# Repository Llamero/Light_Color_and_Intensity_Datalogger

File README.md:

# Data Logger: Temperature, Pressure, Humidity, Light Intensity and Color

## Summary:

This is an open-source data logger that can record air temperature, air pressure, relative humidity, visible light instensity, near-infrared light intensity, and visible light color (RGB).  This data logger can record at up to 1 Hz onto a FAT32 formatted SD card.  At 1Hz and with a full battery pack (6 AAs) the data logger should run for 200+ days on a single pack (depending on the SD card), with lower sampling frequencies increasing the duration to a maximum of >800 days (depending on the SD card).  The light sensors employ an autogain feature with the intensity sensor having a 600,000,000:1 dynamic range, and a minimum sensitivity at about 1.0 nW/cm2.

Windows users: Use this program to format SD cards >32 GB http://www.ridgecrop.demon.co.uk/index.htm?guiformat.htm

For information on ordering, assembly, and programming, please see the instruction manual. 

Development of this data logger was funded by NIH P30-EY003176-32

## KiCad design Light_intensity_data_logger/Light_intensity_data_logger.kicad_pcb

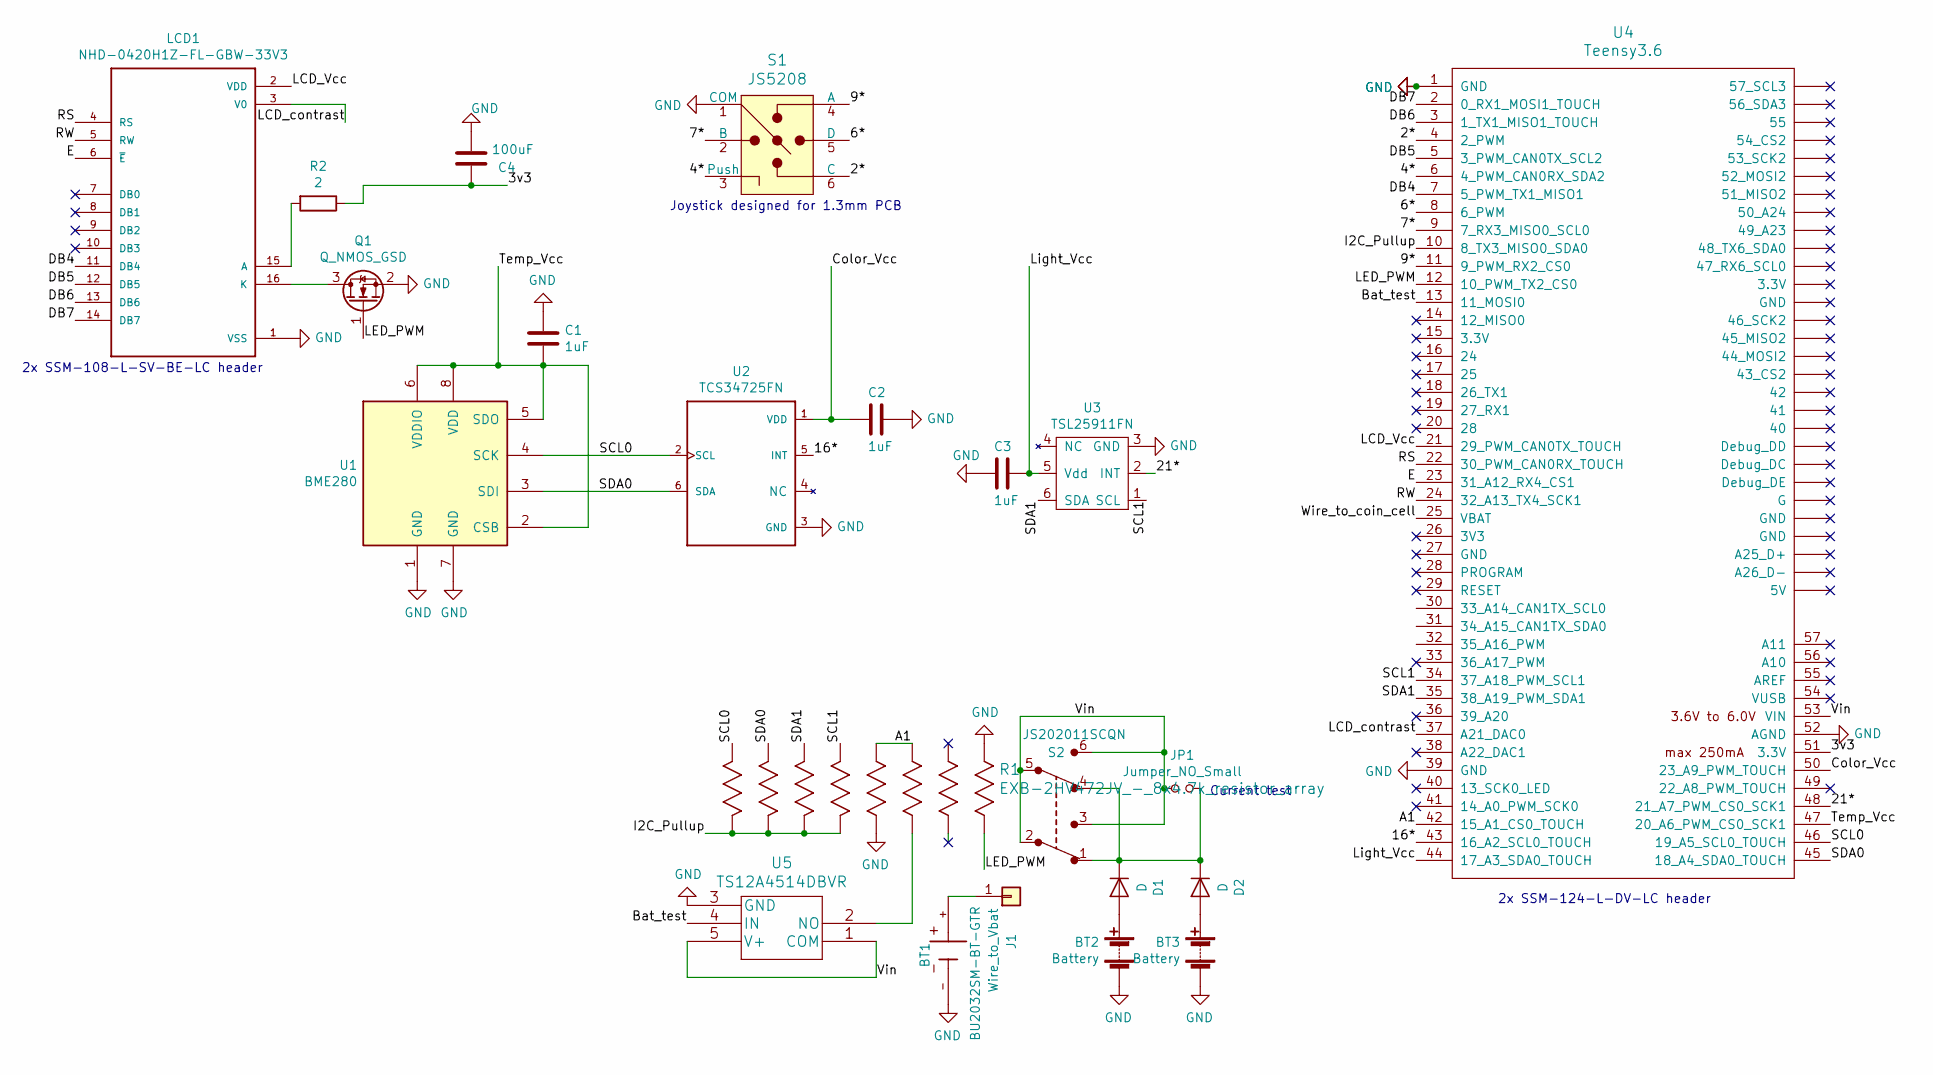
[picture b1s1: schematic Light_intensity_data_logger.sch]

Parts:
BT1: BU2032SM-BT-GTR; Part# BU2032SM-BT-GCT-ND
BT2, BT3: Battery; BH3AAW-Battery_wire_pads; Part# SBH331A-ND
C1, C2, C3: 1uF; C_0603; Part# 445-1604-1-ND
C4: 100uF; C_1206; Part# 1276-1782-1-ND
D1, D2: D; D_SOD-323; Part# CUS10S30H3FCT-ND
J1: Wire_to_Vbat; SolderWirePad_single_SMD_5x10mm
JP1: Jumper_NO_Small; Banana_Jack_2Pin
LCD1: NHD-0420H1Z-FL-GBW-33V3; NHD-0420H1Z-FL-GBW-33V3_Display_with_Header; Part# NHD-0420H1Z-FL-GBW-33V3
Q1: Q_NMOS_GSD; SOT-23; Part# BSS806NH6327XTSA1CT-ND
R1: EXB-2HV472JV_-_8x4.7k_resistor_array; 4816P-1-472LF; Part# 4816P-1-472LFCT-ND
R2: 2; R_0603; Part# 311-2.00HRCT-ND
S1: JS5208; Switch_Nav_12.4x12.4mm_SMD_JS5208; Part# EG4561-ND
S2: JS202011SCQN; Switch_Slide_JS202011SCQN; Part# 401-2002-1-ND
U1: BME280; Pressure_Sensor_LGA-8_2.5x2.5mm_BME280; Part# 828-1063-1-ND
U2: TCS34725FN; TCS34725; Part# TCS34725FNCT-ND
U3: TSL25911FN; Part# TSL25911FNCT-ND
U4: Teensy3.6; Teensy3.6_doublewide_header; Part# 1568-1465-ND
U5: TS12A4514DBVR; SOT-23-5

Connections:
/2*: S1.6 (C), U4.4 (2_PWM)
/3v3: C4.1, R2.1, U4.51 (3.3V)
/4*: S1.3 (Push), U4.6 (4_PWM_CAN0RX_SDA2)
/6*: S1.5 (D), U4.8 (6_PWM)
/7*: S1.2 (B), U4.9 (7_RX3_MISO0_SCL0)
/9*: S1.4 (A), U4.11 (9_PWM_RX2_CS0)
/16*: U2.5 (INT), U4.43 (16_A2_SCL0_TOUCH)
/21*: U3.2 (INT), U4.48 (21_A7_PWM_CS0_SCK1)
/A1: R1.3, R1.4, U4.42 (15_A1_CS0_TOUCH)
/Bat_test: U4.13 (11_MOSI0), U5.4 (IN)
/Color_Vcc: C2.2, U2.1 (VDD), U4.50 (23_A9_PWM_TOUCH)
/DB4: LCD1.11 (DB4), U4.7 (5_PWM_TX1_MISO1)
/DB5: LCD1.12 (DB5), U4.5 (3_PWM_CAN0TX_SCL2)
/DB6: LCD1.13 (DB6), U4.3 (1_TX1_MISO1_TOUCH)
/DB7: LCD1.14 (DB7), U4.2 (0_RX1_MOSI1_TOUCH)
/E: LCD1.6 (~E~), U4.23 (31_A12_RX4_CS1)
/I2C_Pullup: R1.9, R1.10, R1.11, R1.12, U4.10 (8_TX3_MISO0_SDA0)
/LCD_Vcc: LCD1.2 (VDD), U4.21 (29_PWM_CAN0TX_TOUCH)
/LCD_contrast: LCD1.3 (V0), U4.37 (A21_DAC0)
/LED_PWM: Q1.1 (G), R1.16, U4.12 (10_PWM_TX2_CS0)
/Light_Vcc: C3.1, U3.5 (Vdd), U4.44 (17_A3_SDA0_TOUCH)
/RS: LCD1.4 (RS), U4.22 (30_PWM_CAN0RX_TOUCH)
/RW: LCD1.5 (RW), U4.24 (32_A13_TX4_SCK1)
/SCL0: R1.8, U1.4 (SCK), U2.2 (SCL), U4.46 (19_A5_SCL0_TOUCH)
/SCL1: R1.5, U3.1 (SCL), U4.34 (37_A18_PWM_SCL1)
/SDA0: R1.7, U1.3 (SDI), U2.6 (SDA), U4.45 (18_A4_SDA0_TOUCH)
/SDA1: R1.6, U3.6 (SDA), U4.35 (38_A19_PWM_SDA1)
/Temp_Vcc: C1.2, U1.2 (CSB), U1.5 (SDO), U1.6 (VDDIO), U1.8 (VDD), U4.47 (20_A6_PWM_CS0_SCK1)
/Vin: JP1.1, S2.2, S2.3, S2.5, S2.6, U4.53 (VIN), U5.1 (COM), U5.5 (V+)
GND: BT1.-, BT2.2 (-), BT3.2 (-), C1.1, C2.1, C3.2, C4.2, LCD1.1 (VSS), Q1.2 (S), R1.1, R1.13, S1.1 (COM), U1.1 (GND), U1.7 (GND), U2.3 (GND), U3.3 (GND), U4.1 (GND), U4.39 (GND), U4.52 (AGND), U5.3 (GND)
unnamed: BT1.+, J1.1
unnamed: BT2.1 (+), D1.2 (A)
unnamed: BT3.1 (+), D2.2 (A)
unnamed: D1.1 (K), D2.1 (K), JP1.2, S2.1, S2.4
unnamed: LCD1.15 (A), R2.2
unnamed: LCD1.16 (K), Q1.3 (D)
unnamed: R1.14, U5.2 (NO)

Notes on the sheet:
Current test
Joystick designed for 1.3mm PCB
2x SSM-108-L-SV-BE-LC header
2x SSM-124-L-DV-LC header

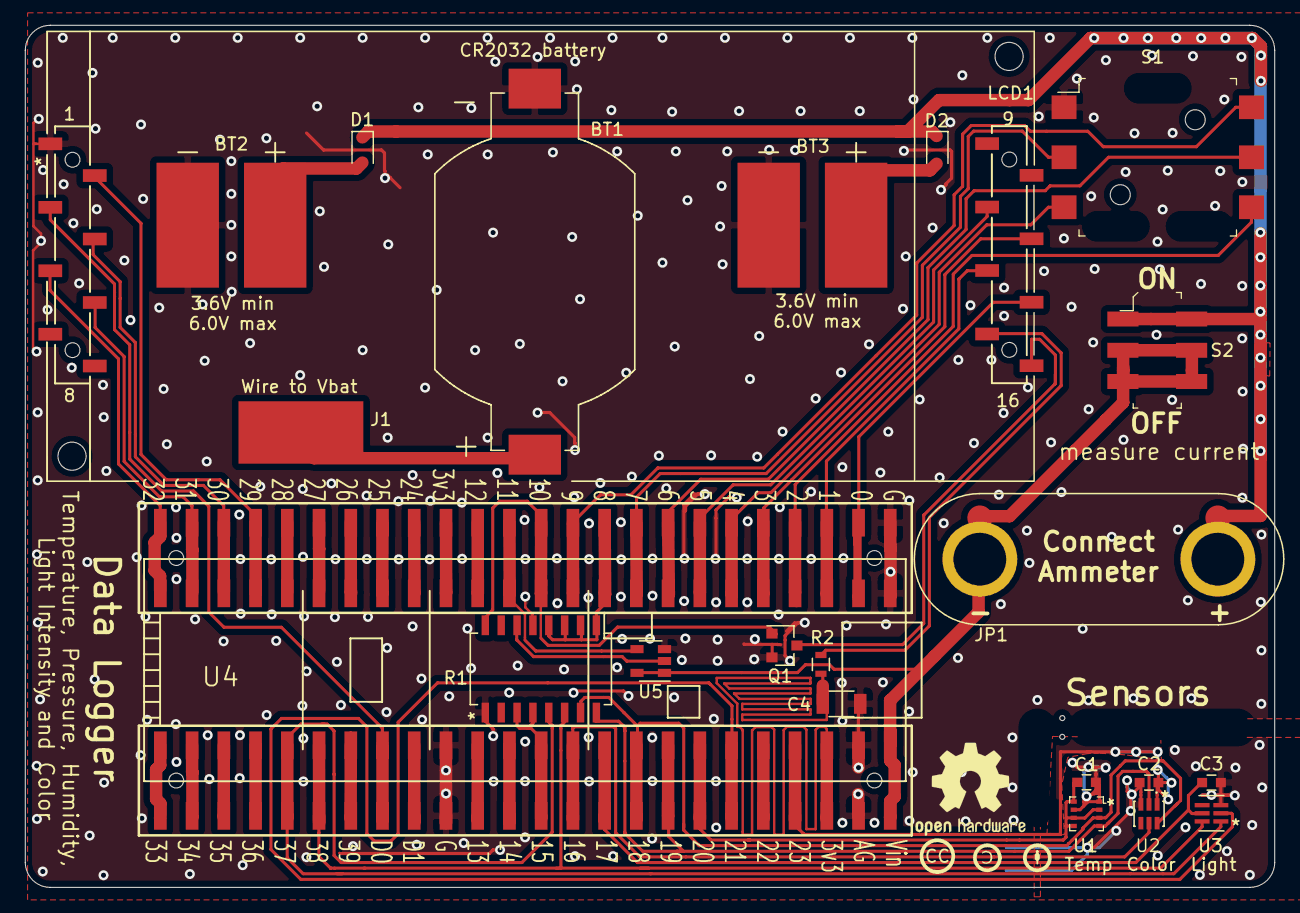
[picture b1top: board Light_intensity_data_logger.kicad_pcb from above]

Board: 2 copper layers, 100.0 x 69.0 mm, 22 parts (0 on the bottom side), 37 nets.

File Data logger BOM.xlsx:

Part ID | Value | Footprint | Manufacturer | Manufacturer Part # | Digikey Part # | Quantity | Link
BT1 | BU2032SM-BT-GTR | Ben_Custom:BU2032SM-BT-GTR | MPD (Memory Protection Devices) | BU2032SM-BT-GTR | BU2032SM-BT-GCT-ND | 1 | https://www.digikey.com/product-detail/en/mpd-memory-protect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
BT2, BT3 | Battery | Ben_Custom:BH3AAW-Battery_wire_pads | MPD (Memory Protection Devices) | SBH331A | SBH331A-ND | 2 | https://www.digikey.com/products/en?keywords=SBH331A-ND
C1-C3 | 1uF | Capacitors_SMD:C_0603 | TDK Corporation | C1608X7R1C105K080AC | 445-1604-1-ND | 3 | https://www.digikey.com/products/en?keywords=445-1604-1-ND
C4 | 100uF | Capacitors_SMD:C_1206 | Samsung Electro-Mechanics | CL31A107MQHNNNE | 1276-1782-1-ND | 1 | https://www.digikey.com/products/en?keywords=1276-1782-1-ND
D1-D2 | D | Diodes_SMD:D_SOD-323 | Toshiba Semiconductor and Storage | CUS10S30,H3F | CUS10S30H3FCT-ND | 2 | https://www.digikey.com/products/en?keywords=CUS10S30H3FCT-ND
LCD1 | NHD-0420H1Z-FL-GBW-33V3 | Ben_Custom:NHD-0420H1Z-FL-GBW-33V3_Display_with_Header | Newhaven Display Intl | NHD-0420H1Z-FL-GBW-33V3 | NHD-0420H1Z-FL-GBW-33V3-ND | 1 | https://www.digikey.com/products/en?keywords=NHD-0420H1Z-FL-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
LCD Header | SSM-108-L-SV-BE-LC | Ben_Custom:NHD-0420H1Z-FL-GBW-33V3_Display_with_Header | Samtec Inc. | SSM-108-L-SV-BE-LC | SSM-108-L-SV-BE-LC-ND | 2 | https://www.digikey.com/products/en?keywords=SSM-108-L-SV-BE-LC-ND
LCD Standoff | 970100244 | Ben_Custom:NHD-0420H1Z-FL-GBW-33V3_Display_with_Header | Würth Elektronik | 970100244 | 732-12845-ND | 2 | https://www.digikey.com/products/en?keywords=732-12845-ND
LCD Bolt | MPMS 002 0005 PH | Ben_Custom:NHD-0420H1Z-FL-GBW-33V3_Display_with_Header | B&F Fastener Supply | MPMS 002 0005 PH | H738-ND | 100 | https://www.digikey.com/products/en/hardware-fasteners-acces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
Q1 | Q_NMOS_GSD | TO_SOT_Packages_SMD:SOT-23 | Infineon Technologies | BSS806NH6327XTSA1 | BSS806NH6327XTSA1CT-ND | 1 | https://www.digikey.com/products/en?keywords=BSS806NH6327XTSA1CT-ND
R1 | EXB-2HV472JV_-_8x4.7k_resistor_array | Ben_Custom:4816P-1-472LF | Bourns Inc. | 4816P-1-472LF | 4816P-1-472LFCT-ND | 1 | https://www.digikey.com/products/en?keywords=4816P-1-472LFCT-ND
R2 | 2 Ohm | Resistors_SMD:R_0603 | Yageo | RC0603FR-072RL | 311-2.00HRCT-ND | 1 | https://www.digikey.com/products/en?keywords=311-2.00HRCT-ND
S1 | JS5208 | digikey-footprints:Switch_Nav_12.4x12.4mm_SMD_JS5208 | E-Switch | JS5208 | EG4561-ND | 1 | https://www.digikey.com/products/en?keywords=EG4561-ND
S2 | JS202011SCQN | digikey-footprints:Switch_Slide_JS202011SCQN | C&K | JS202011SCQN | 401-2002-1-ND | 1 | https://www.digikey.com/products/en?keywords=401-2002-1-ND
U1 | BME280 | digikey-footprints:Pressure_Sensor_LGA-8_2.5x2.5mm_BME280 | Bosch Sensortec | BME280 | 828-1063-1-ND | 1 | https://www.digikey.com/products/en?keywords=828-1063-1-ND
U2 | TCS34725FN | Ben_Custom:TCS34725 | ams | TCS34725FN | TCS34725FNCT-ND | 1 | https://www.digikey.com/products/en?keywords=TCS34725FNCT-ND
U3 | TSL25911FN | Ben_Custom:TSL25911FN | ams | TSL25911FN | TSL25911FNCT-ND | 1 | https://www.digikey.com/products/en?keywords=TSL25911FNCT-ND
U4 | Teensy3.6 | Ben_Custom:Teensy3.6_doublewide_header | SparkFun Electronics | DEV-14058 | 1568-1465-ND | 1 | https://www.digikey.com/products/en?keywords=1568-1465-ND
U5 | TS12A4514DBVR | TO_SOT_Packages_SMD:SOT-23-5 |  | TS12A4514DBVR | 296-24201-1-ND | 1 | https://www.digikey.com/products/en?keywords=296-24201-1-ND
Teensy Header | SSM-124-L-DV-LC | Ben_Custom:Teensy3.6_doublewide_header | Samtec Inc. | SSM-124-L-DV-LC | SSM-124-L-DV-LC-ND | 2 | https://www.digikey.com/products/en?keywords=SSM-124-L-DV-LC-ND
# of decives: | 1.0

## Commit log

2020-01-10 Changed to smaller bypass caps
2020-01-10 Add power switch and Vbat sense
2020-01-11 Add joystick and display
2020-01-15 Add claw headers and initial PCB layout
2020-01-17 Sensors connected in PCB layout
2020-01-17 Teensy flipped sensors rewired
2020-01-17 All but left monitor wired
2020-01-17 Complete routed draft - pass DRC other than courtyard
2020-01-17 First draft complete
2020-01-17 Vias optimized
2020-01-18 License info and annotations added
2020-01-18 Removed extra ground trace
2020-01-19 Parts numbered in order, courtyards fixed, bigger banana pads
2020-01-19 Rewire LED gate to PWM channel
2020-01-19 Switch to 1uF caps for sensors per light sensor spec sheet
2020-01-19 Switch to 1uF caps
2020-01-19 Gerber files added
2020-01-20 Replace sensor edge cut with NPTH
2020-01-20 Ordered version
2020-01-20 Remove extra info from switch BOM
2020-01-22 PCBWay compatible - max PCB dim <100mm
2020-01-23 Started draft of Data logger code
2020-01-23 LCD implemented as tabbed library - contrast pin function working
2020-01-24 Add Adafruit libaries, specify wire port
2020-01-24 Sync to computer time on upload, add sensor system variables
2020-01-24 Confirmation if display is present by checking busy flag and CGRAM address
2020-01-24 Changed Strings to char arrays to be compatible with Arduino
2020-01-24 Remove "const" since not compatible with libraries
2020-01-24 Fully power down LCD and DAC if LCD fails to boot
2020-01-24 Remove conversions in analog writes to make them not dependent on fixed resolution
2020-01-24 Add backlight and support for adjusting to set analog write resolution
2020-01-24 Add backlight capability and automatic conversion to analog resolution
2020-01-24 Add adjustable analog resolution - freq is automatically calcualted to max for 24 MHz
2020-01-25 set max value to true bit range, rather than bit range+1
2020-01-25 Turn on backlight on LCD initialize
2020-01-25 Force contrast and backlight intensity inputs to be 0-1
2020-01-25 Add initializing LCD to default contrast value
2020-01-25 Add backlight status flag to initialize
2020-01-25 Add function to fully disable display to lowest power state
2020-01-25 Add function to disable display to lowest power state
2020-01-28 8-pin display working 4-pin not fully functional - missing characters
2020-01-28 Add timeout to busy check, add disable display, add address to device begin
2020-01-28 Add option to select which lines get updated - blank line for missing lines
2020-01-28 fix DAC_en warning
2020-01-28 add comment for Dac_en fix
2020-01-31 Add bat check - DO NOT COMPILE WITH SLOWEST!!!
2020-01-31 4 pin mode working!
    The issue with 4-pin mode is that it is expecting synchronous inputs, and the Teensy is asynchronous. One implementation got all but '0' and '1' to render correctly, while the for loop implementation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
2020-01-31 4-pin LCD option implemented in ino file
2020-01-31 Add Vbat and Vin voltage test
2020-01-31 Revert "Add Vbat and Vin voltage test"
    This reverts commit c4b5c565b3b1f5829fb307e870f01e86cc5f1558.
2020-01-31 Revert "Revert "Add Vbat and Vin voltage test""
    This reverts commit 85e1a66305e13b341a6e999fe05abeda229eac9e.
2020-02-04 Write to SD card - add RTC synced time stamp
2020-02-04 Can be re-initalized to load new configuration settings - fixed overflow issue
2020-02-04 Issue with Snooze.h resolved
    Upgrading to Arduino 1.8.11 and Teensyduino 1.50 made it so that the Teensy 3.6 would enter hibernate and not wake.
    Reverting to Arduino 1.8.10 and Teensyduino 1.48 seemed to resolve the issue.
2020-02-04 Make joystick pins const
2020-02-05 Using modified LiquidCrystalFast.h for stable 4 pin - add begin() timeout
2020-02-05 Add arrays for settings and logging windows
2020-02-05 All windows passed as single array - scroll up works
2020-02-05 Vertical scroll fully implemented with indicator arrows
2020-02-05 Add capability to switch windows left and right
2020-02-05 Fixed µ character and ° character
2020-02-05 Clean up temporary commented blocks
2020-02-06 Add check for next available log file name on boot
2020-02-06 Invald bigChar as library
2020-02-06 Large font start and stop log added - fully implemented
2020-02-06 Temporary switch to timer as alarm seems to block digital
2020-02-07 Driver runs at 52 uA on hibernate
2020-02-07 Wake timer stays synced to RTC clock - 1s hysteresis
2020-02-07 Add safety so that if next log is before now(), next_log does no overflow to large number
2020-02-07 Can now log time at intervals with header
2020-02-08 Fixed MOSFET issue - improved routing
    Changed LCD to 4-pin only to free up pins
    Routed data lines in clusters to leave open contiguous blocks of pins
    Kept DAC0 line above PCB
    Attached light interrupt to pin 21 - valid hibernate digital line
    Used analog switch to pulse Vbat to DAC,
    Put N-mos on GND side of LED.
2020-02-11 Auto gain feature added for light and color sensor
2020-02-11 If not actively logging perform complete autogain routine
2020-02-12 Add trace resistor between 3v3 and backlight cap for RC filtering
    Trace resistor is 0.181 ohm
2020-02-12 This is draft of PCB submitted to PCBWay, logging works!!!
2020-02-12 Logger now uses RTCms() to sync to RTC, and logs to SD
2020-02-13 Power management implemented
    Still need to add ability to cut power to sensors on standby
2020-02-14 Many power saving and SD imporovements
    SD loads in blocks of 512 bytes to improve write speed and save power
    Circular log buffer implemented to allow 512 block writes
    SD missing detection and halt with software reset via joystick.
    Digital wakeups logged during button press help with exit log detection
2020-02-14 More optimizations
    Fixed wake during log on button press
    Made so temp is only read once per BME280 reading
    Removed all serial
    Compiler optmization did not change current draw
2020-02-19 Use memcpy and a single buffer to reduce up time
2020-02-19 Fix double font glitch on STOP LOG
2020-02-26 Updated pins to new PCB format
2020-02-27 Add pulldown resistor to LCD LED PWM pin
    Add pull down resistor so that the LCD LED with default to off if the pin is in a high impedance state.
2020-03-04 Fix bug in hibernate timer
2020-03-04 Remove Vbat check since when Teensy powered off it drew 360µA
2020-03-04 Remove Vbat check circuit
2020-03-04 Get rid of dedub comments - reduce pullup delay to 10 µs
2020-03-07 Re-organize repository
2020-03-07 Create project summary
2020-03-07 Move Teensy.lib file
2020-03-07 Add bill of materials
2020-03-07 Fix bolt equation
2020-03-07 Add creative commons license for PCB and schematic
2020-03-07 Fix directory typo
2020-03-07 Add manual
2020-03-08 Update manual
2020-03-11 Add pdf
2020-03-11 Add sample log files
2020-03-11 Add image
2020-03-11 Add image to README
2020-03-11 Add FAT32 GUI link
2020-03-11 Add grant citation

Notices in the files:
parts and their libraries:
Copyright 2016 Accelerated Designs. All rights reserved.
